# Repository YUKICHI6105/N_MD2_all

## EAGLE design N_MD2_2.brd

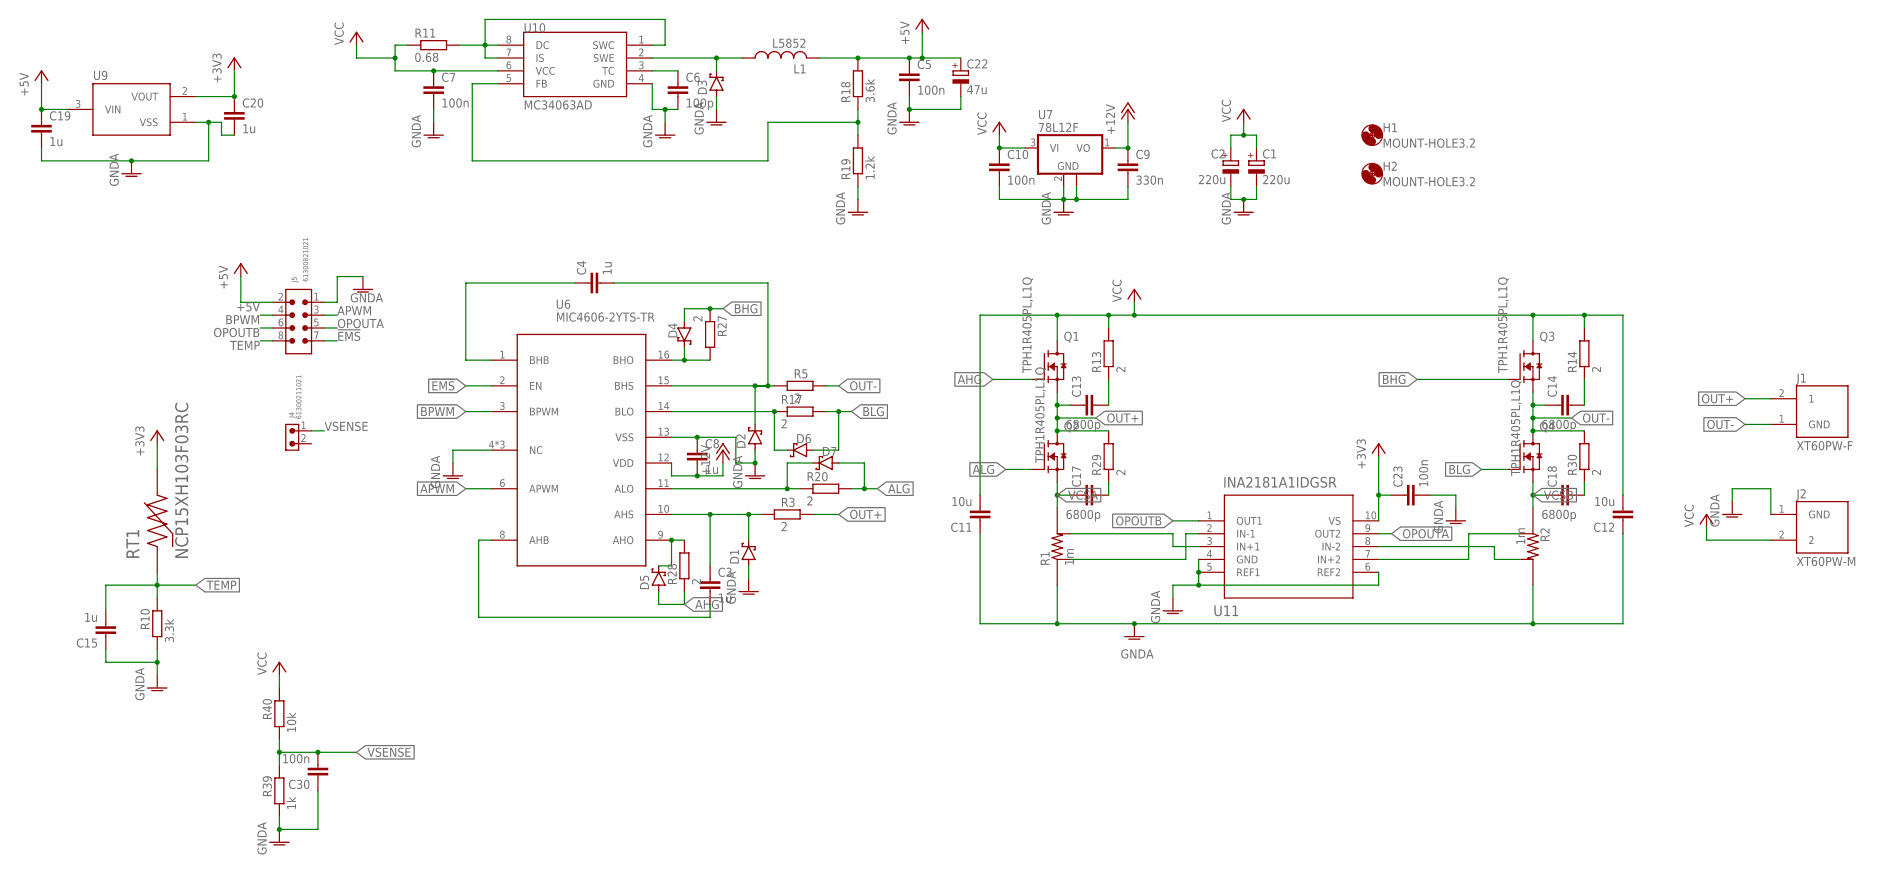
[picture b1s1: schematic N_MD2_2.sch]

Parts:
C1, C2: 220u; E5-10,5
C3, C4, C8, C15, C19, C20: 1u; C0603
C5, C7, C10, C23, C30: 100n; C0603
C6: 100p; C0603
C9: 330n; C0603
C11, C12: 10u; C1210
C13, C14, C17, C18: 6800p; C0603
C22: 47u; E2,5-5
D1, D2, D3, D4, D5, D6, D7: PMEG6010CEJ,115; SOD323_ST
H1, H2: MOUNT-HOLE3.2; 3,2
J1: XT60PW-F; AMASS_XT60PW-F
J2: XT60PW-M; AMASS_XT60PW-M
J4: 61300211021
J5: 61300821021
L1: L5852
Q1, Q2, Q3, Q4: TPH1R405PL,L1Q; SOPADVANCE
R1, R2: 1m; 2512-4PAD
R3, R5, R13, R14, R17, R20, R27, R28, R29, R30: 2; R0603
R10: 3.3k; R0603
R11: 0.68; R1206
R18: 3.6k; R0603
R19: 1.2k; R0603
R39: 1k; R0603
R40: 10k; R0603
RT1: NCP15XH103F03RC; THRMC1005X55N
U6: MIC4606-2YTS-TR; TSSOP16
U7: 78L12F; SOT89
U9: XC6206; SOT95P240X110-3
U10: MC34063AD; SOIC8
U11: INA2181A1IDGSR; DGS10

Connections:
!EMS: J5.7, U6.2 (EN)
+3V3: C20.1, C23.1, RT1.2, U9.2 (VOUT), U11.10 (VS)
+5V: C5.1, C19.1, C22.+, J5.2, L1.P$2 (2), R18.2, U9.3 (VIN)
+12V: C8.2, C9.1, U6.12 (VDD), U7.1 (VO)
AHG: D5.A, Q1.4 (G), R28.1
ALG: D7.A, Q2.4 (G), R20.2
APWM: J5.3, U6.6 (APWM)
BHG: D4.A, Q3.4 (G), R27.1
BLG: D6.A, Q4.4 (G), R17.2
BPWM: J5.4, U6.3 (BPWM)
GNDA: C1.-, C2.-, C5.2, C6.2, C7.2, C8.1, C9.2, C10.2, C11.1, C12.1, C15.1, C19.2, C20.2, C22.-, C23.2, C30.1, D1.A, D2.A, D3.A, J2.1 (GND), J5.1, R1.1, R1.2 (1), R2.3 (2), R2.4 (2), R10.1, R19.1, R39.1, U6.4 (NC), U6.5 (NC), U6.7 (NC), U6.13 (VSS), U7.2 (GND), U7.2@1 (GND), U9.1 (VSS), U10.4 (GND), U11.4 (GND), U11.5 (REF1), U11.6 (REF2)
unnamed: C17.2, R29.1
unnamed: C18.2, R30.1
unnamed: C3.1, D1.C, R3.1, U6.10 (AHS)
unnamed: C3.2, U6.8 (AHB)
unnamed: C4.2, D2.C, R5.1, U6.15 (BHS)
unnamed: C4.1, U6.1 (BHB)
unnamed: C14.2, R14.1
unnamed: D6.C, R17.1, U6.14 (BLO)
unnamed: C13.2, R13.1
unnamed: D7.C, R20.1, U6.11 (ALO)
unnamed: R1.6 (4), U11.3 (IN+1)
unnamed: R2.5 (3), U11.7 (IN+2)
unnamed: D3.C, L1.P$1 (1), U10.2 (SWE)
unnamed: C6.1, U10.3 (TC)
unnamed: R18.1, R19.2, U10.5 (FB)
unnamed: R2.6 (4), U11.8 (IN-2)
unnamed: R11.2, U10.1 (SWC), U10.7 (IS), U10.8 (DC)
unnamed: R1.5 (3), U11.2 (IN-1)
unnamed: D4.C, R27.2, U6.16 (BHO)
unnamed: D5.C, R28.2, U6.9 (AHO)
OPOUTA: J5.5, U11.9 (OUT2)
OPOUTB: J5.6, U11.1 (OUT1)
OUT+: C13.1, J1.2 (1), Q1.1 (S), Q1.2 (S), Q1.3 (S), Q2.5 (D), Q2.6 (D), Q2.7 (D), Q2.8 (D), Q2.9 (D), R3.2, R29.2
OUT-: C14.1, J1.1 (GND), Q3.1 (S), Q3.2 (S), Q3.3 (S), Q4.5 (D), Q4.6 (D), Q4.7 (D), Q4.8 (D), Q4.9 (D), R5.2, R30.2
TEMP: C15.2, J5.8, R10.2, RT1.1
VCC: C1.+, C2.+, C7.1, C10.1, C11.2, C12.2, J2.2, Q1.5 (D), Q1.6 (D), Q1.7 (D), Q1.8 (D), Q1.9 (D), Q3.5 (D), Q3.6 (D), Q3.7 (D), Q3.8 (D), Q3.9 (D), R11.1, R13.2, R14.2, R40.2, U7.3 (VI), U10.6 (VCC)
VCSA: C17.1, Q2.1 (S), Q2.2 (S), Q2.3 (S), R1.3 (2), R1.4 (2)
VCSB: C18.1, Q4.1 (S), Q4.2 (S), Q4.3 (S), R2.1, R2.2 (1)
VSENSE: C30.2, J4.1, R39.2, R40.1

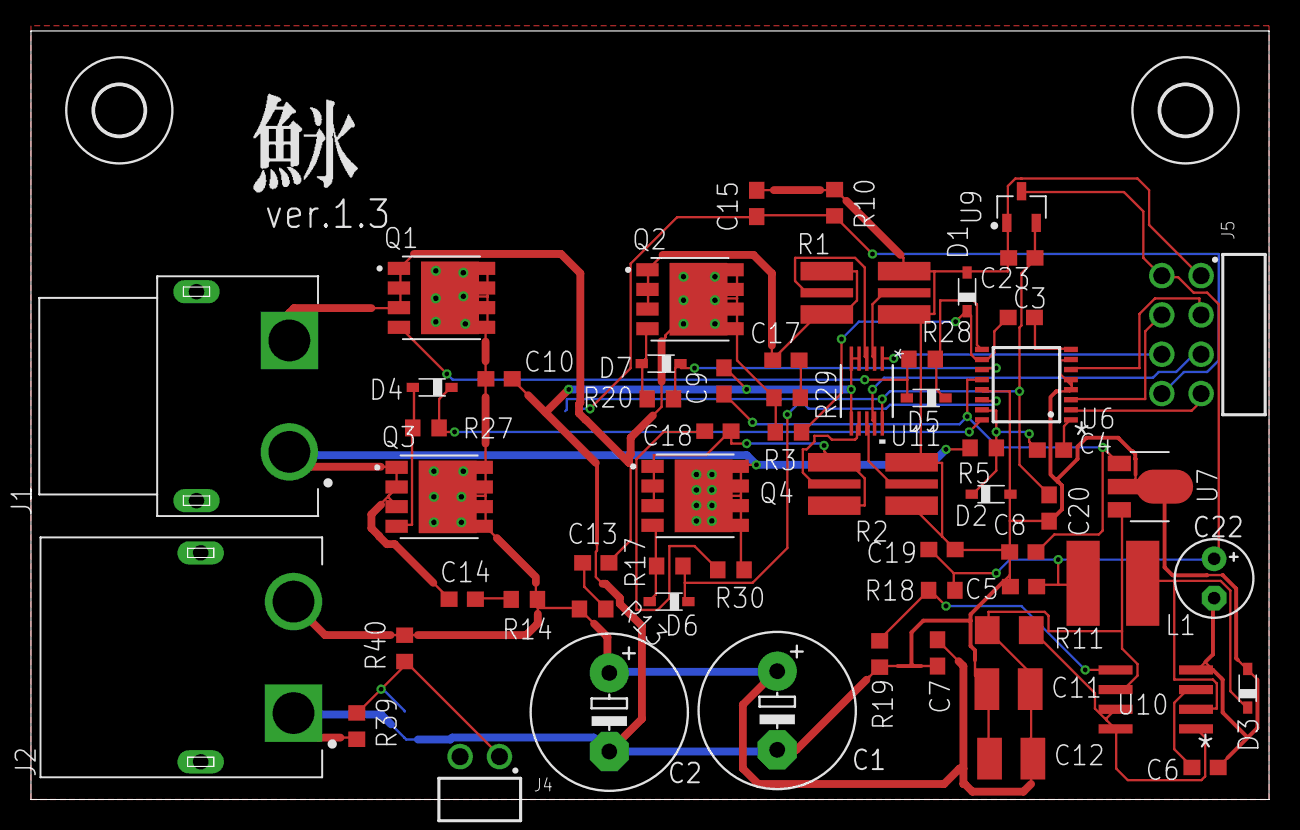
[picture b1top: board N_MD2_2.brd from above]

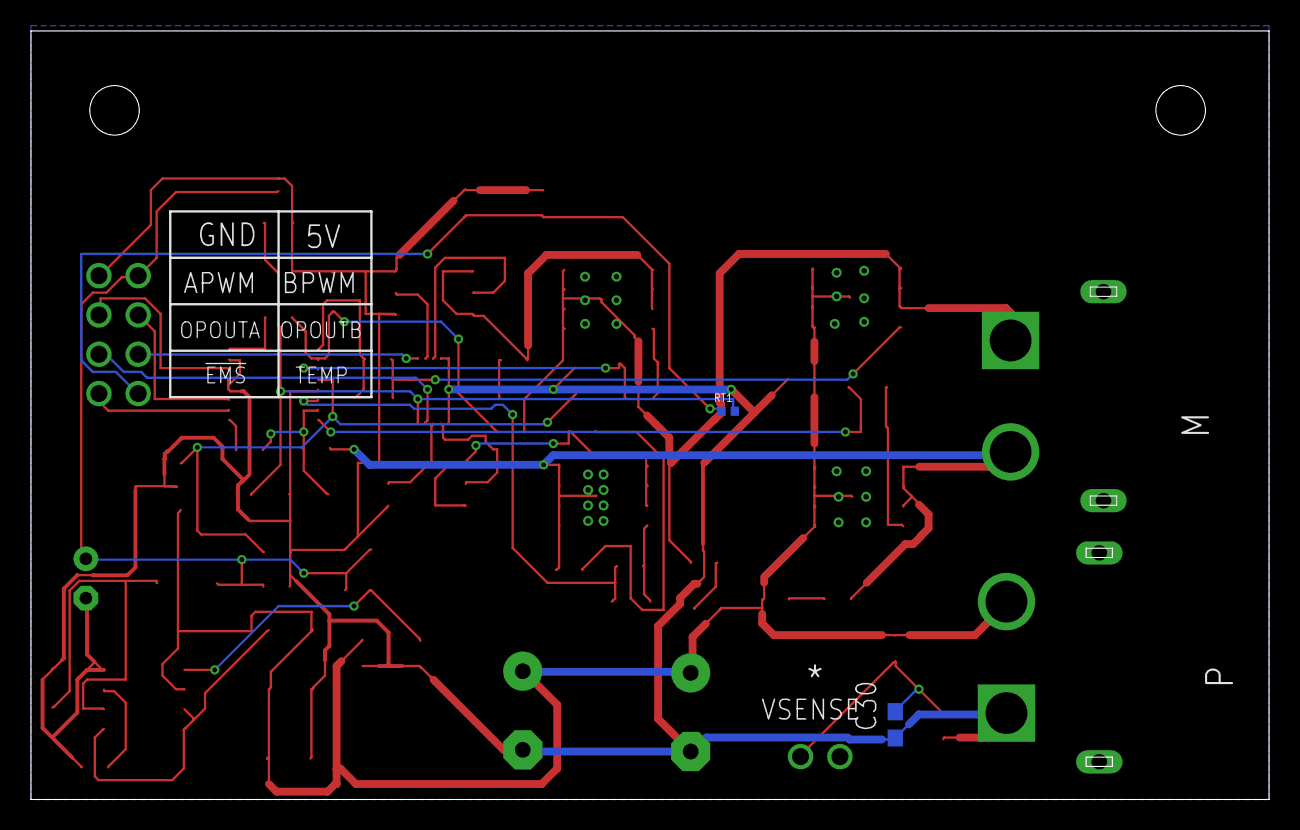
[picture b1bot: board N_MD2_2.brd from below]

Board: 2 copper layers, 80.0 x 49.7 mm, 64 parts (2 on the bottom side), 40 nets.

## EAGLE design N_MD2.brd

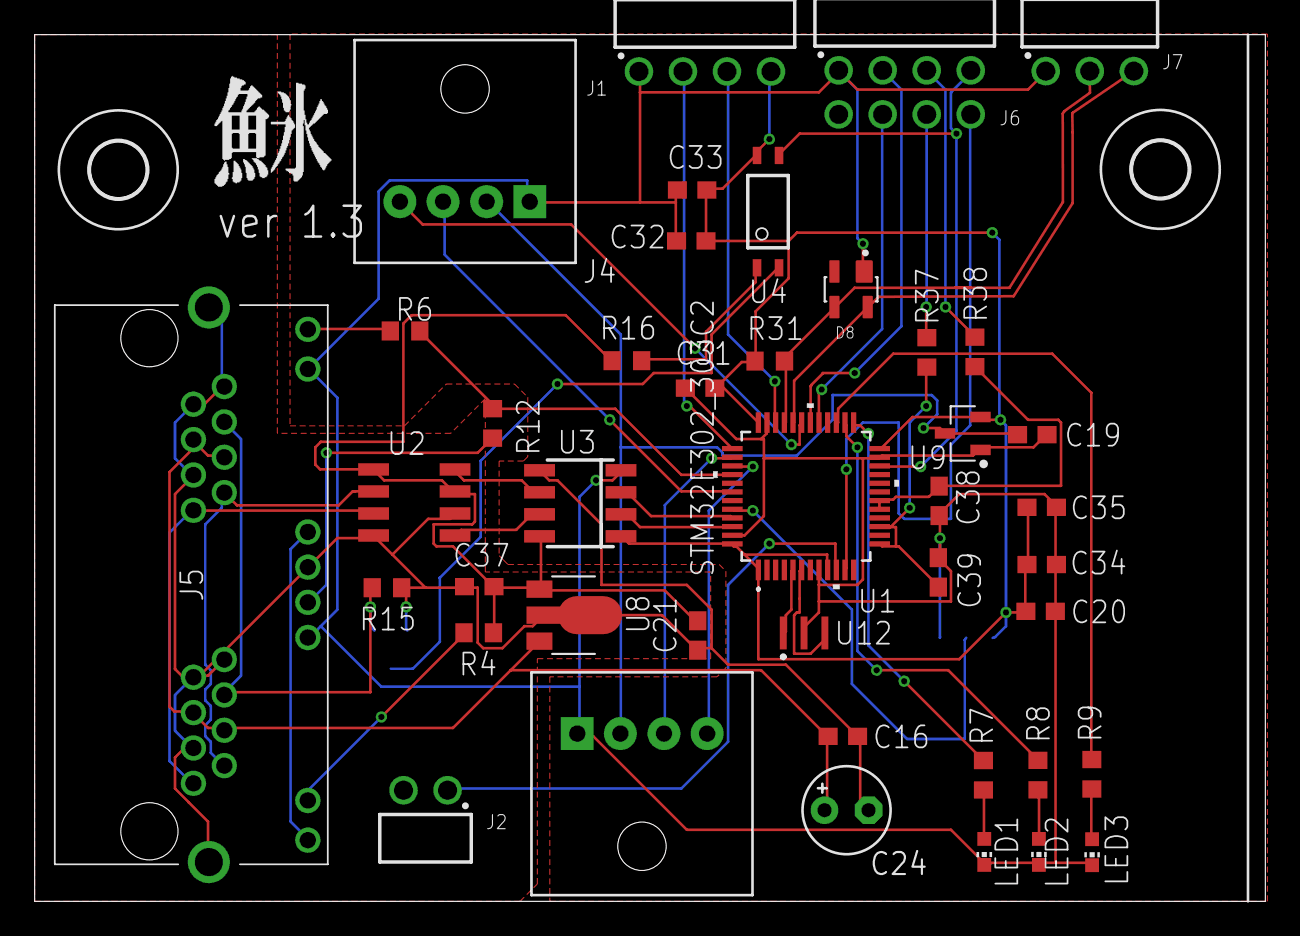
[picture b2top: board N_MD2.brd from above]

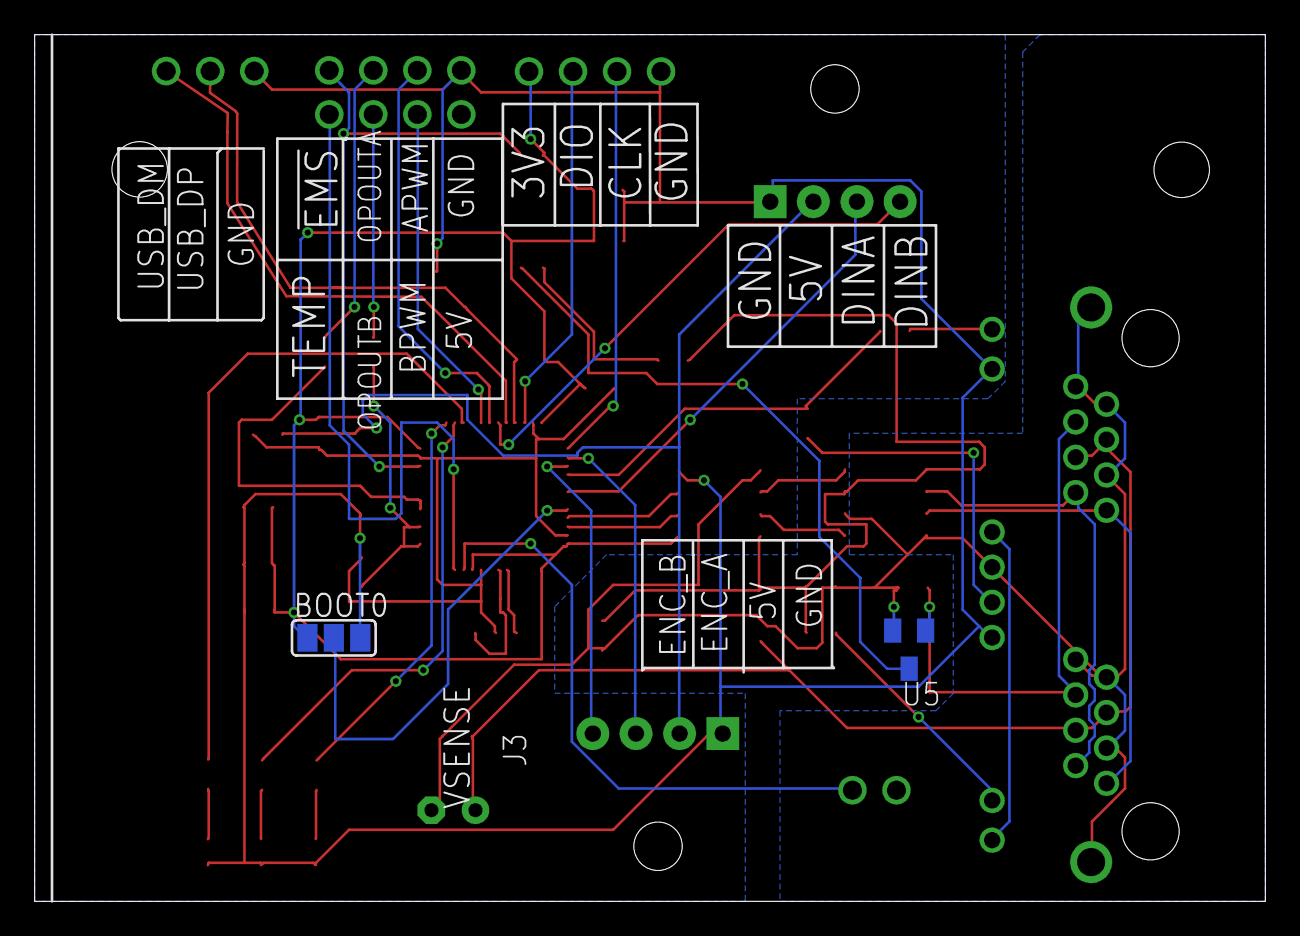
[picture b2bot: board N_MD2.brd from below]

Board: 2 copper layers, 71.0 x 50.0 mm, 46 parts (2 on the bottom side), 46 nets.

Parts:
BOOT0: SJ_2
C16, C21, C31, C32, C33: 100n; C0603
C19, C20, C35: 1u; C0603
C24: 47u; E2,5-5
C34: 10n; C0603
C37: 330n; C0603
C38, C39: 330p; C0603
D8: SP0503BAHTG; SOT143
H1, H2: MOUNT-HOLE3.2; 3,2
J1: 61300411021
J2: 61300211021
J3, J4: EP2.5-4-SIDE; CONN4_1744426-4
J5: RJHSE-5381-02; RJHSE538102
J6: 61300821021
J7: 61300311021
LED1: RED; CHIP-LED0603
LED2: YELLOW; CHIP-LED0603
LED3: GREEN; CHIP-LED0603
R4: 100; R0603
R6, R12: 180; R0603
R7, R8, R9: 1.2k; R0603
R15: 10k; R0603
R16: 470; R0603
R31: 1k5; R0603
R37, R38: 1k; R0603
U1: STM32F302_303C2; LQFP48-7X7MM
U2: NCV7351D1E; SO08
U3: SI8621EC-B-IS; SO08
U4: TLP291; MINI-FLAT-4
U5: BSS138BK; SOT23
U8: 78L05F; SOT89
U9: XC6206; SOT95P240X110-3
U12: CSTNE_GH5L

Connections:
5V_ISO: C21.2, C37.1, R4.1, R16.1, U2.3, U2.5, U3.8, U8.1
!EMS: J6.7, U1.22, U4.3
+3V3: BOOT0.1, C20.1, C31.2, C32.2, C33.2, C34.2, C35.2, J1.4, R31.1, U1.1, U1.9, U1.24, U1.36, U1.48, U3.1, U4.4, U9.2
+5V: C19.1, J3.2, J4.2, U9.3
APWM: J6.3, U1.30
BOOT0: BOOT0.2, U1.44
BPWM: J6.4, U1.29
CAN_H: J5.A1, J5.B1, U2.7
CAN_L: J5.A2, J5.B2, U2.6
CAN_RX: U1.45, U3.3
CAN_TX: U1.46, U3.2
DIN_A: J4.3, U1.42
DIN_B: J4.4, U1.31
ENC_A: J3.3, U1.38
ENC_B: J3.4, U1.39
GNDA: BOOT0.3, C19.2, C20.2, C31.1, C32.1, C33.1, C34.1, C35.1, C38.1, C39.1, D8.1, J1.1, J3.1, J4.1, J5.A11, J5.B11, J6.1, J7.1, LED1.C, LED2.C, LED3.C, U1.8, U1.23, U1.35, U1.47, U3.4, U9.1, U12.2
GNDIO: C16.2, C21.1, C24.-, C37.2, J5.A3, J5.A7, J5.A8, J5.A9, J5.B3, J5.B7, J5.B8, J5.MH1, J5.MH2, R15.1, U2.2, U2.8, U3.5, U5.2, U8.2, U8.2@1
ISENSEA: C38.2, R38.2, U1.17, U1.18
ISENSEB: C39.2, R37.2, U1.13, U1.15
LED_CAN: R6.2, R12.1, U1.40
LED_GREEN: R7.2, U1.25
LED_RED: R9.2, U1.27
LED_YELLOW: R8.2, U1.26
unnamed: J5.B10, R4.2
unnamed: J5.A10, J5.B9
unnamed: LED1.A, R7.1
unnamed: LED2.A, R8.1
unnamed: LED3.A, R9.1
unnamed: J5.A12, R6.1
unnamed: J5.B12, R12.2
unnamed: U2.1, U3.7
unnamed: C16.1, C24.+, J5.A4, J5.A5, J5.B4, J5.B5, U8.3
unnamed: U2.4, U3.6
unnamed: J5.A6, J5.B6, R15.2, U5.1
unnamed: U4.2, U5.3
unnamed: R16.2, U4.1
unnamed: U1.5, U12.1
unnamed: U1.6, U12.3
OPOUTA: J6.5, R38.1
OPOUTB: J6.6, R37.1
SWCLK: J1.2, U1.37
SWDIO: J1.3, U1.34
TEMP: J6.8, U1.11
USB_DM: D8.4, J7.3, U1.32
USB_DP: D8.3, J7.2, R31.2, U1.33
VSENSE: J2.1, U1.10

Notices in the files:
parts and their libraries:
Wurth_Connectors_WR-PHD: Copyright: Würth Elektronik
COPYRIGHT: Copyright (C) 2016 Accelerated Designs. All rights reserved
COPYRIGHT: Copyright (C) 2018 Accelerated Designs. All rights reserved
